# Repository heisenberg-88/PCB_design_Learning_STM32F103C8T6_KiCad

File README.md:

# PCB_design_Learning_STM32F103C8T6_KiCad
STM32F103C8T6 Custom PCB design on KiCad

Software used : KiCad EDA https://www.kicad.org/

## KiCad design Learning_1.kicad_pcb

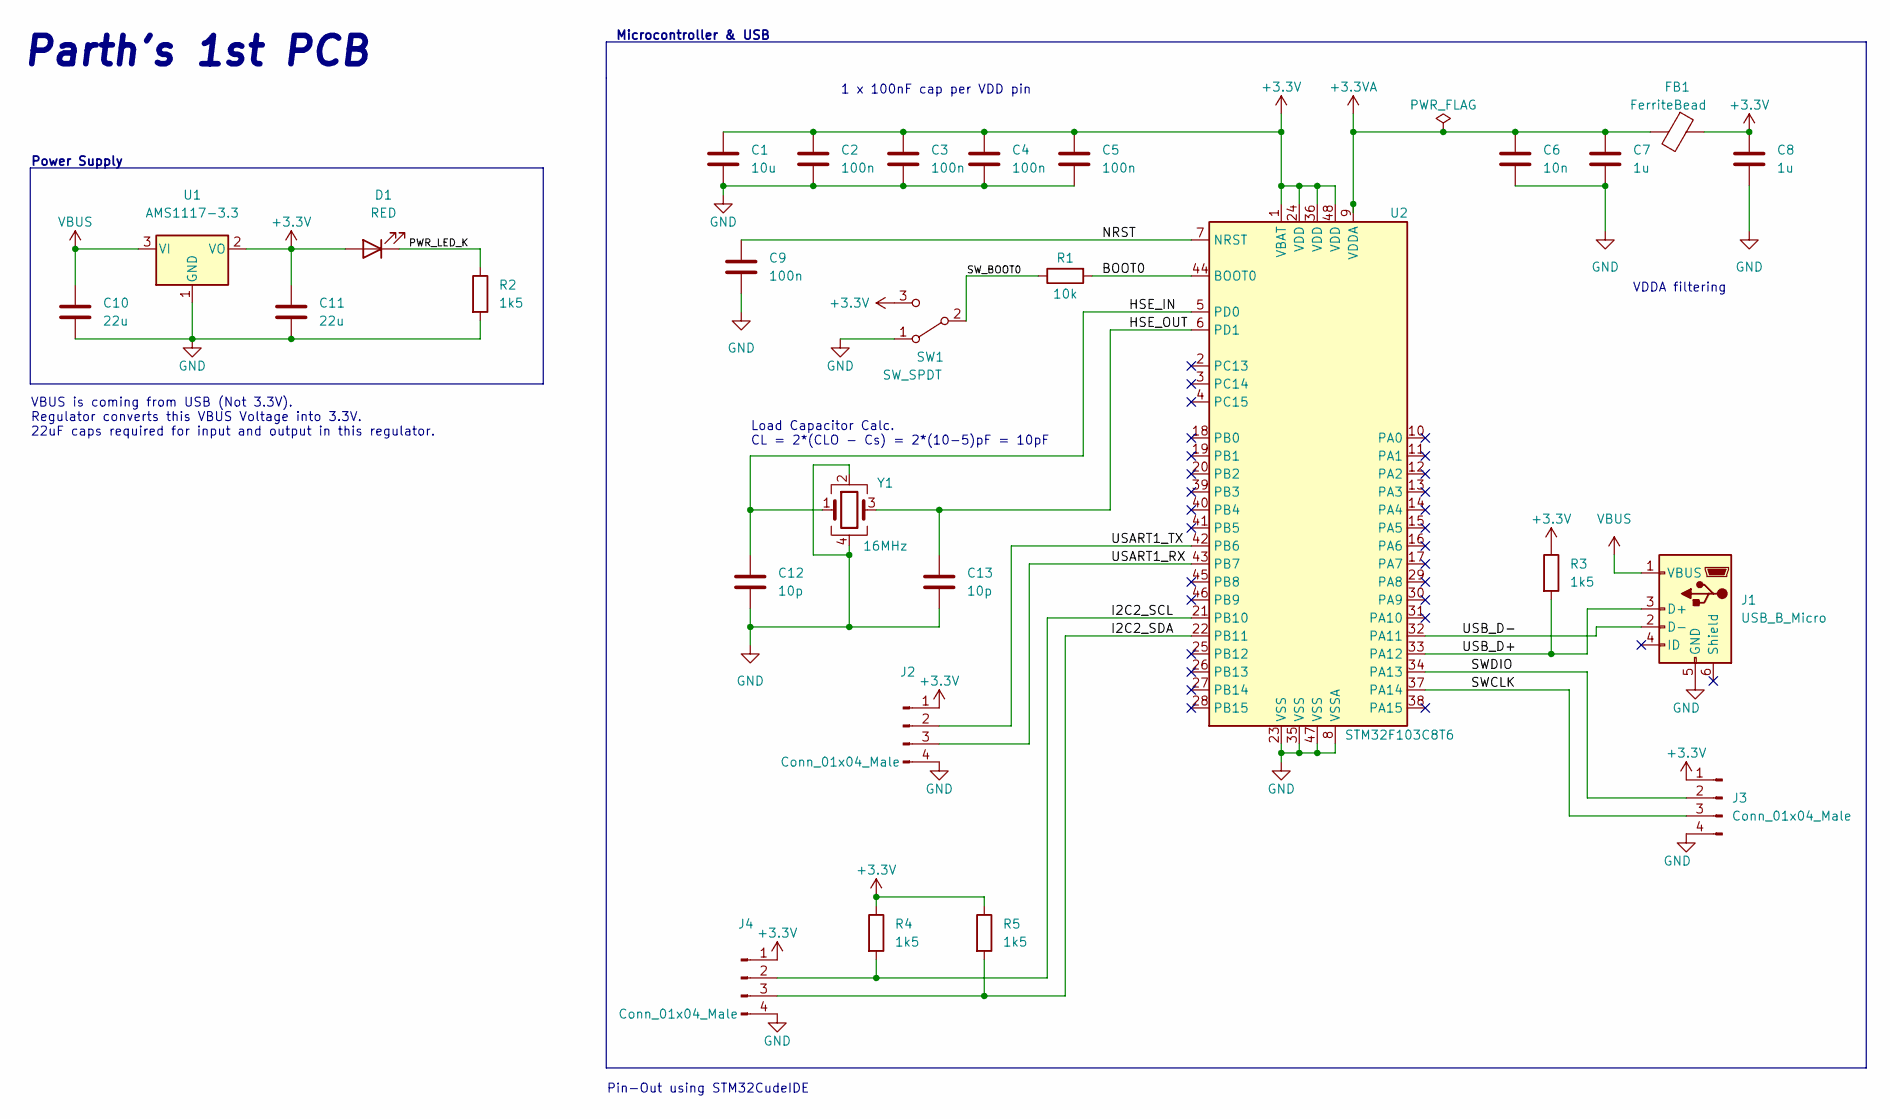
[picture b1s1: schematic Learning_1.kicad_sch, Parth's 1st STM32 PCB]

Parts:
C1: 10u; C_0603_1608Metric
C2, C3, C4, C5, C9: 100n; C_0402_1005Metric
C6: 10n; C_0402_1005Metric
C7, C8: 1u; C_0402_1005Metric
C10, C11: 22u; C_0805_2012Metric
C12, C13: 10p; C_0402_1005Metric
D1: RED; LED_0603_1608Metric
FB1: FerriteBead; L_0603_1608Metric
J1: USB_B_Micro; USB_Micro-B_Wuerth_629105150521
J2, J3, J4: Conn_01x04_Male; PinHeader_1x04_P2.54mm_Vertical
R1: 10k; R_0402_1005Metric
R2, R3, R4, R5: 1k5; R_0402_1005Metric
SW1: SW_SPDT; SW_Lever_1P2T_NKK_GW12LxH
U1: AMS1117-3.3; SOT-223-3_TabPin2
U2: STM32F103C8T6; LQFP-48_7x7mm_P0.5mm
Y1: 16MHz; Crystal_SMD_3225-4Pin_3.2x2.5mm

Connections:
+3.3V: C1.1, C2.1, C3.1, C4.1, C5.1, C8.1, C11.1, D1.2 (A), FB1.1, J2.1, J3.1, J4.1, R3.1, R4.1, R5.1, SW1.3 (C), U1.2 (VO), U2.1 (VBAT), U2.24 (VDD), U2.36 (VDD), U2.48 (VDD)
+3.3VA: C6.1, C7.1, FB1.2, U2.9 (VDDA)
/BOOT0: R1.2, U2.44 (BOOT0)
/HSE_IN: C12.1, U2.5 (PD0), Y1.1
/HSE_OUT: C13.1, U2.6 (PD1), Y1.3
/I2C2_SCL: J4.2, R4.2, U2.21 (PB10)
/I2C2_SDA: J4.3, R5.2, U2.22 (PB11)
/NRST: C9.1, U2.7 (NRST)
/PWR_LED_K: D1.1 (K), R2.1
/SWCLK: J3.3, U2.37 (PA14)
/SWDIO: J3.2, U2.34 (PA13)
/SW_BOOT0: R1.1, SW1.2 (B)
/USART1_RX: J2.3, U2.43 (PB7)
/USART1_TX: J2.2, U2.42 (PB6)
/USB_D+: J1.3 (D+), R3.2, U2.33 (PA12)
/USB_D-: J1.2 (D-), U2.32 (PA11)
GND: C1.2, C2.2, C3.2, C4.2, C5.2, C6.2, C7.2, C8.2, C9.2, C10.2, C11.2, C12.2, C13.2, J1.5 (GND), J2.4, J3.4, J4.4, R2.2, SW1.1 (A), U1.1 (GND), U2.8 (VSSA), U2.23 (VSS), U2.35 (VSS), U2.47 (VSS), Y1.2, Y1.4
VBUS: C10.1, J1.1 (VBUS), U1.3 (VI)

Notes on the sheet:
Microcontroller & USB
VDDA filtering
1 x 100nF cap per VDD pin
Parth's 1st PCB
Power Supply
Pin-Out using STM32CudeIDE
Load Capacitor Calc. CL = 2*(CLO - Cs) = 2*(10-5)pF = 10pF
VBUS is coming from USB (Not 3.3V). Regulator converts this VBUS Voltage into 3.3V. 22uF caps required for input and output in this regulator.

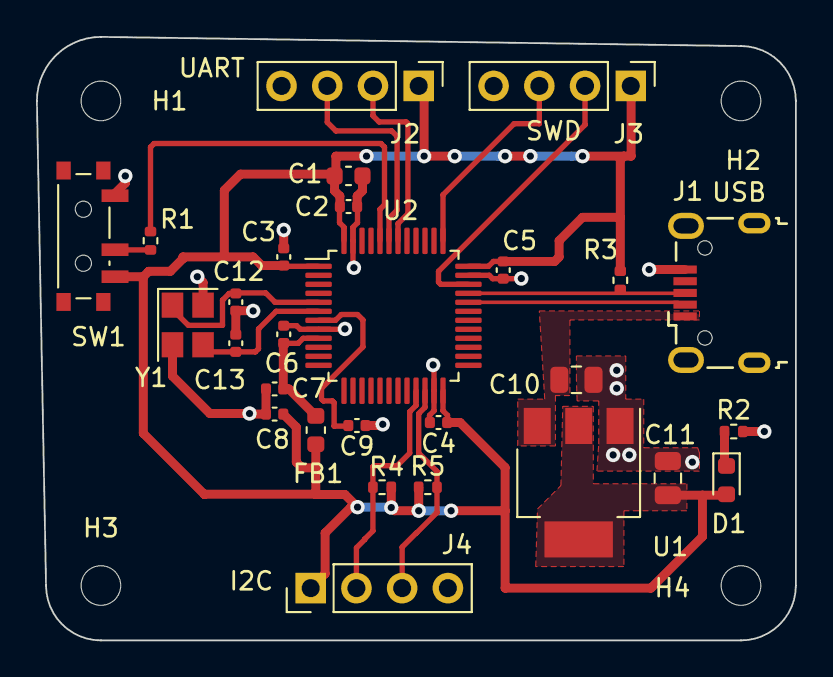
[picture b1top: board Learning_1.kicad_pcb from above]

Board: 2 copper layers, 42.2 x 33.5 mm, 32 parts (0 on the bottom side), 18 nets.

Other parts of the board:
H1, H2, H3, H4: MountingHole; MountingHole_2.2mm_M2

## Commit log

2022-12-26 Schematic
2023-01-15 gbr files for mfg
